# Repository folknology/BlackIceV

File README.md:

# BlackIce V
BlackIce V is the 6th generation of a long line of OpenSource Hardware FPGA boards designed by the myStorm community since 2016. Unlike it's predecessors based on the Ice40 HX range, the 'V' is based on the Lattice Ice40 UltraPlus up5K and offers great new features like DSP blocks and generous internal SRAM.

Current status is hardware design, you can see the developments we are making on my regular streams :
*  [Live Stream, 8pm BST](https://www.twitch.tv/folknology)
* [Historic streams](https://www.youtube.com/watch?v=79OoLG_Dxk0&list=PLXS9jyX9czzodpJNL-szsMfl0rOrZk4B7)
Or at the join us at the [myStorm community forum](https://forum.mystorm.uk)

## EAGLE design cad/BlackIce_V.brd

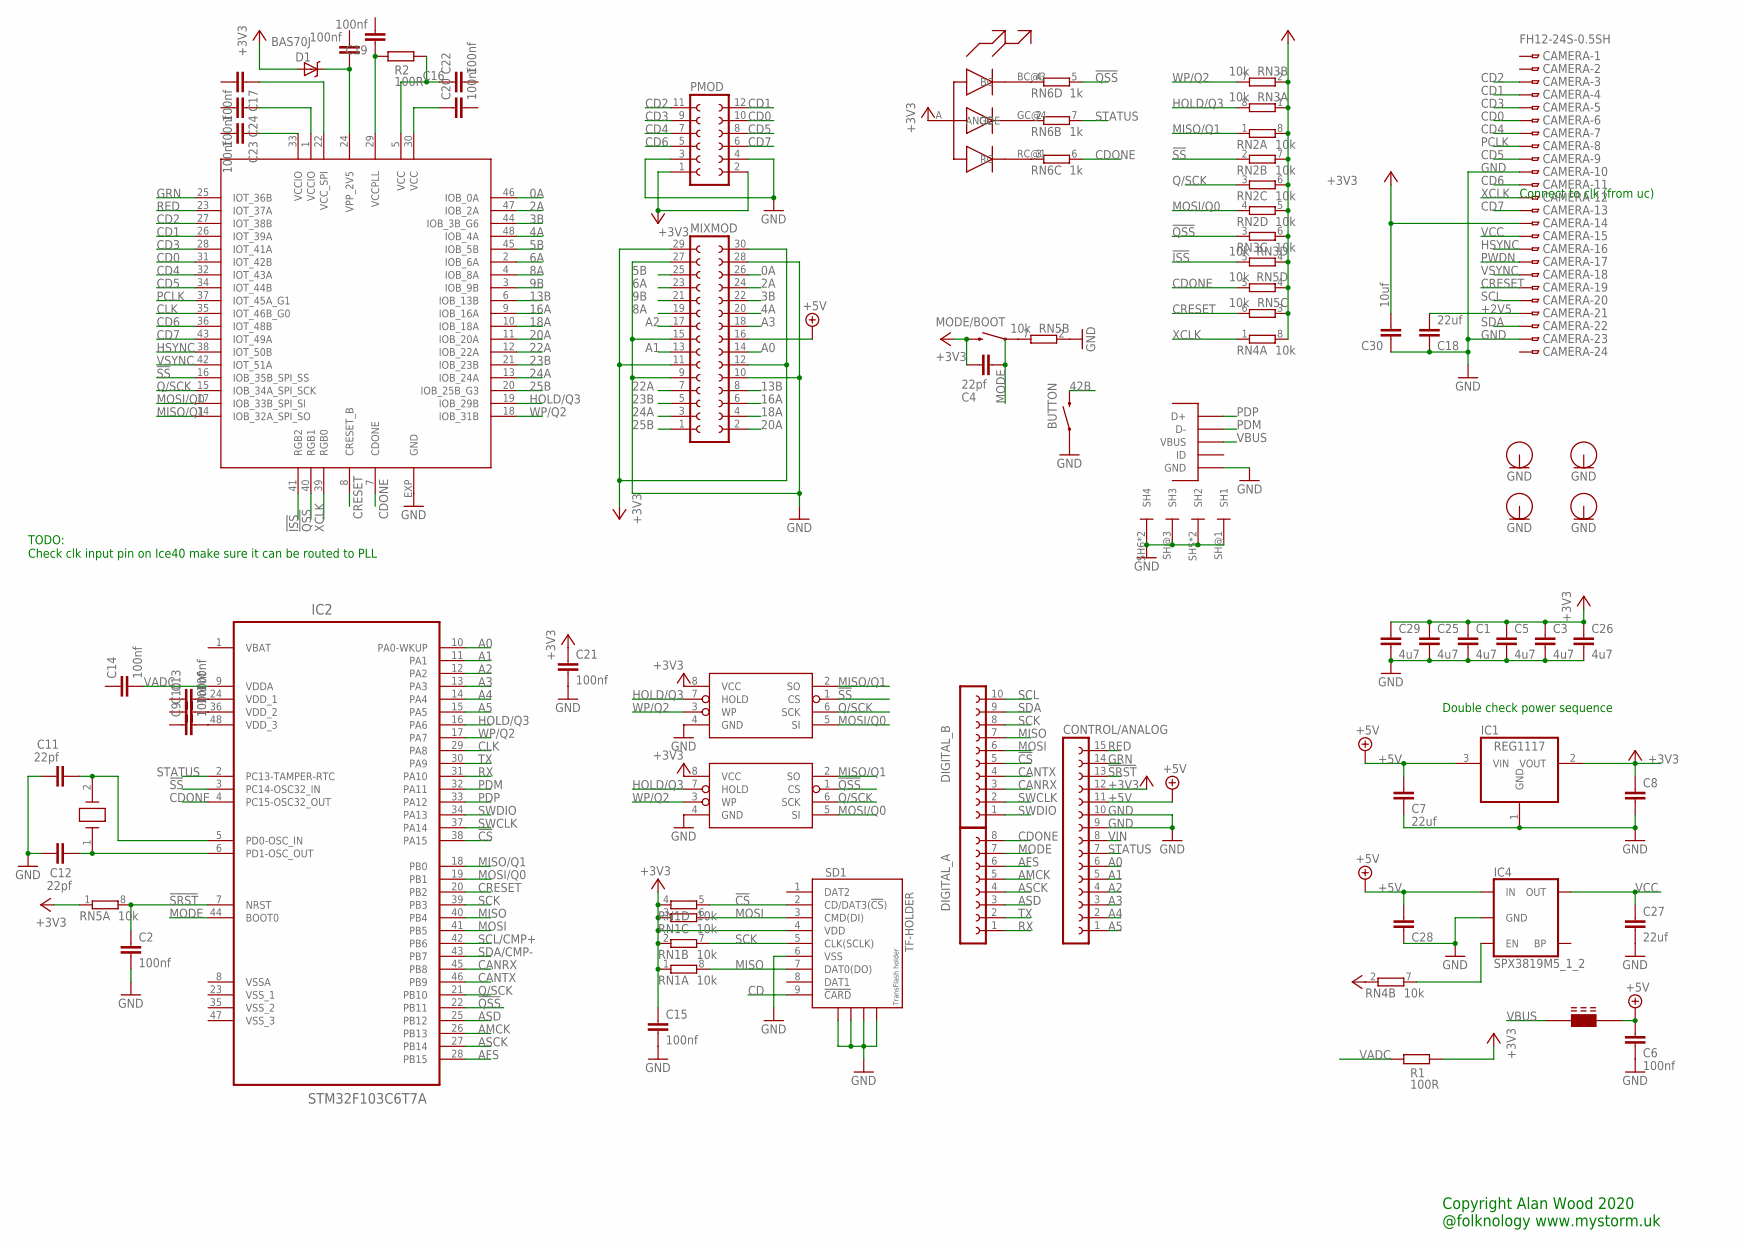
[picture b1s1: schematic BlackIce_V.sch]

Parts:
BUTTON: SWITCH-MOMENTARY-2SMD-1101NE; TACTILE-SWITCH-1101NE
C1, C3, C5, C25, C26, C29: 4u7; C0603
C2, C6, C9, C10, C13, C14, C15, C16, C17, C19, C20, C21, C22, C23, C24: 100nf; C0402
C4, C11, C12: 22pf; C0603
C7, C8, C18, C27, C28: 22uf; C0603
C30: 10uf; C0603
CAMERA: FH12-24S-0.5SH
CONTROL/ANALOG: FE15-1; FE15
D1: BAS70J; SOD-323
DIGITAL_A: FE08-1; FE08
DIGITAL_B: FE10-1; FE10
FB1: FERRITE_BEAD; 0603
H1, H2, H3, H4: HOLE2.5MM; 2.5MM-HOLE
IC1: REG1117; SOT223
IC2: STM32F103C6T7A; QFP50P900X900X160-48N
IC3: ICE40UP5K; QFN48
IC4: SPX3819M5_1_2; SOT23-5
IC5, IC6: AT25SDF041A; SOIC-8-NARROW
MIXMOD: FE15-2
MODE/BOOT: SWITCH-MOMENTARY-2SMD-1101NE; TACTILE-SWITCH-1101NE
PMOD: FE06-2W
R1, R2: 100R; R0402
RN1, RN2, RN3, RN4, RN5: 10k; 0603-ARV
RN6: 1k; 0603-ARV
SD1: TF-HOLDER; TF-PULL
U$1: FCI-MICROUSB-B-PEG; MICROUSB-B-PEG
U$4: RGB-PLCC-4; PLCC-4-SMALL
X1: HC49UP

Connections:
0A: IC3.46 (IOB_0A), MIXMOD.26
2A: IC3.47 (IOB_2A), MIXMOD.24
3B: IC3.44 (IOB_3B_G6), MIXMOD.22
4A: IC3.48 (IOB_4A), MIXMOD.20
5B: IC3.45 (IOB_5B), MIXMOD.25
6A: IC3.2 (IOB_6A), MIXMOD.23
8A: IC3.4 (IOB_8A), MIXMOD.19
9B: IC3.3 (IOB_9B), MIXMOD.21
13B: IC3.6 (IOB_13B), MIXMOD.8
16A: IC3.9 (IOB_16A), MIXMOD.6
18A: IC3.10 (IOB_18A), MIXMOD.4
20A: IC3.11 (IOB_20A), MIXMOD.2
22A: IC3.12 (IOB_22A), MIXMOD.7
23B: IC3.21 (IOB_23B), MIXMOD.5
24A: IC3.13 (IOB_24A), MIXMOD.3
25B: IC3.20 (IOB_25B_G3), MIXMOD.1
42B: BUTTON.2
!CS: DIGITAL_B.5, IC2.38 (PA15), RN1.5 (2), SD1.2 (CD/DAT3(!CS!))
!ISS: IC3.41 (RGB2), RN3.5 (2)
!QSS: IC2.22 (PB11), IC3.40 (RGB1), IC6.1 (CS), RN3.3 (1), RN6.5 (2)
!SRST: C2.1, CONTROL/ANALOG.13, IC2.7 (NRST), RN5.8 (2)
!SS: IC2.3 (PC14-OSC32_IN), IC3.16 (IOB_35B_SPI_SS), IC5.1 (CS), RN2.2 (1)
+2V5: C16.1, C18.1, CAMERA.21, D1.C, IC3.24 (VPP_2V5)
+3V3: C1.1, C3.1, C4.2, C5.1, C8.1, C15.1, C21.1, C25.1, C26.1, C29.1, C30.2, CAMERA.14, CONTROL/ANALOG.12, D1.A, IC1.2 (VOUT), IC5.8 (VCC), IC6.8 (VCC), MIXMOD.11, MIXMOD.12, MIXMOD.29, MIXMOD.30, MODE/BOOT.2, PMOD.1, PMOD.2, R1.1, RN1.1, RN1.2 (1), RN1.3 (1), RN1.4 (1), RN2.5 (2), RN2.6 (2), RN2.7 (2), RN2.8 (2), RN3.1, RN3.2 (1), RN3.4 (1), RN3.6 (2), RN4.2 (1), RN4.8 (2), RN5.1, RN5.3 (1), RN5.4 (1), SD1.4 (VDD), U$4.A (ANODE)
+5V: C6.2, C7.2, C28.2, CONTROL/ANALOG.11, FB1.2, IC1.3 (VIN), IC4.1 (IN), MIXMOD.16
A0: CONTROL/ANALOG.6, IC2.10 (PA0-WKUP), MIXMOD.14
A1: CONTROL/ANALOG.5, IC2.11 (PA1), MIXMOD.13
A2: CONTROL/ANALOG.4, IC2.12 (PA2), MIXMOD.17
A3: CONTROL/ANALOG.3, IC2.13 (PA3), MIXMOD.18
A4: CONTROL/ANALOG.2, IC2.14 (PA4)
A5: CONTROL/ANALOG.1, IC2.15 (PA5)
AFS: DIGITAL_A.6, IC2.28 (PB15)
AMCK: DIGITAL_A.5, IC2.26 (PB13)
ASCK: DIGITAL_A.4, IC2.27 (PB14)
ASD: DIGITAL_A.3, IC2.25 (PB12)
CANRX: DIGITAL_B.3, IC2.45 (PB8)
CANTX: DIGITAL_B.4, IC2.46 (PB9)
CD: SD1.9 (!CARD)
CD0: CAMERA.6, IC3.31 (IOT_42B), PMOD.10
CD1: CAMERA.4, IC3.26 (IOT_39A), PMOD.12
CD2: CAMERA.3, IC3.27 (IOT_38B), PMOD.11
CD3: CAMERA.5, IC3.28 (IOT_41A), PMOD.9
CD4: CAMERA.7, IC3.32 (IOT_43A), PMOD.7
CD5: CAMERA.9, IC3.34 (IOT_44B), PMOD.8
CD6: CAMERA.11, IC3.36 (IOT_48B), PMOD.5
CD7: CAMERA.13, IC3.43 (IOT_49A), PMOD.6
CDONE: DIGITAL_A.8, IC2.4 (PC15-OSC32_OUT), IC3.7 (CDONE), RN5.5 (2), RN6.6 (2)
CLK: IC2.29 (PA8), IC3.35 (IOT_46B_G0)
CRESET: CAMERA.19, IC2.20 (PB2), IC3.8 (CRESET_B), RN5.6 (2)
GND: BUTTON.1, C1.2, C2.2, C3.2, C5.2, C6.1, C7.1, C8.2, C11.1, C12.1, C15.2, C18.2, C21.2, C25.2, C26.2, C27.2, C28.1, C29.2, C30.1, CAMERA.10, CAMERA.23, CONTROL/ANALOG.9, CONTROL/ANALOG.10, H1.P$1, H2.P$1, H3.P$1, H4.P$1, IC1.1 (GND), IC3.EXP (GND), IC4.2 (GND), IC5.4 (GND), IC6.4 (GND), MIXMOD.9, MIXMOD.10, MIXMOD.15, MIXMOD.27, MIXMOD.28, PMOD.3, PMOD.4, RN5.2 (1), SD1.6 (VSS), SD1.S1, SD1.S2, SD1.S3, SD1.S4, U$1.P$5 (GND), U$1.SH5 (SH2), U$1.SH6 (SH4), U$1.SH@1 (SH1), U$1.SH@2 (SH2), U$1.SH@3 (SH3), U$1.SH@4 (SH4)
GRN: CONTROL/ANALOG.14, IC3.25 (IOT_36B)
HOLD/Q3: IC2.16 (PA6), IC3.19 (IOB_29B), IC5.7 (HOLD), IC6.7 (HOLD), RN3.8 (2)
HSYNC: CAMERA.16, IC3.38 (IOT_50B)
MISO: DIGITAL_B.7, IC2.40 (PB4), RN1.8 (2), SD1.7 (DAT0(DO))
MISO/Q1: IC2.18 (PB0), IC3.14 (IOB_32A_SPI_SO), IC5.2 (SO), IC6.2 (SO), RN2.1
MODE: C4.1, DIGITAL_A.7, IC2.44 (BOOT0)
MOSI: DIGITAL_B.6, IC2.41 (PB5), RN1.6 (2), SD1.3 (CMD(DI))
MOSI/Q0: IC2.19 (PB1), IC3.17 (IOB_33B_SPI_SI), IC5.5 (SI), IC6.5 (SI), RN2.4 (1)
unnamed: RN6.4 (1), U$4.BC@3 (BC)
unnamed: RN6.2 (1), U$4.GC@4 (GC)
unnamed: RN6.3 (1), U$4.RC@1 (RC)
unnamed: MODE/BOOT.1, RN5.7 (2)
unnamed: IC4.3 (EN), RN4.7 (2)
unnamed: C12.2, IC2.6 (PD1-OSC_OUT), X1.1 (X1)
unnamed: C11.2, IC2.5 (PD0-OSC_IN), X1.2 (X2)
unnamed: C13.2, IC2.24 (VDD_1)
unnamed: C10.2, IC2.36 (VDD_2)
unnamed: C9.2, IC2.48 (VDD_3)
unnamed: C23.1, IC3.33 (VCCIO)
unnamed: C24.1, IC3.1 (VCCIO)
unnamed: C17.1, IC3.22 (VCC_SPI)
unnamed: C19.1, IC3.29 (VCCPLL), R2.2
unnamed: C22.1, IC3.5 (VCC), R2.1
unnamed: C20.1, IC3.30 (VCC)
PCLK: CAMERA.8, IC3.37 (IOT_45A_G1)
PDM: IC2.32 (PA11), U$1.P$2 (D-)
PDP: IC2.33 (PA12), U$1.P$3 (D+)
PWDN: CAMERA.17
Q/SCK: IC2.21 (PB10), IC3.15 (IOB_34A_SPI_SCK), IC5.6 (SCK), IC6.6 (SCK), RN2.3 (1)
RED: CONTROL/ANALOG.15, IC3.23 (IOT_37A)
RX: DIGITAL_A.1, IC2.31 (PA10)
SCK: DIGITAL_B.8, IC2.39 (PB3), RN1.7 (2), SD1.5 (CLK(SCLK))
SCL: CAMERA.20, DIGITAL_B.10
SCL/CMP+: IC2.42 (PB6)
SDA: CAMERA.22, DIGITAL_B.9
SDA/CMP-: IC2.43 (PB7)
STATUS: CONTROL/ANALOG.7, IC2.2 (PC13-TAMPER-RTC)
SWCLK: DIGITAL_B.2, IC2.37 (PA14)
SWDIO: DIGITAL_B.1, IC2.34 (PA13)
TX: DIGITAL_A.2, IC2.30 (PA9)
VADC: C14.2, IC2.9 (VDDA), R1.2
VBAT: IC2.1 (VBAT)
VBUS: FB1.1, U$1.P$1 (VBUS)
VCC: C27.1, CAMERA.15, IC4.5 (OUT)
VIN: CONTROL/ANALOG.8
VSYNC: CAMERA.18, IC3.42 (IOT_51A)
WP/Q2: IC2.17 (PA7), IC3.18 (IOB_31B), IC5.3 (WP), IC6.3 (WP), RN3.7 (2)
XCLK: CAMERA.12, IC3.39 (RGB0), RN4.1

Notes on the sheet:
Double check power sequence
TODO: Check clk input pin on Ice40 make sure it can be routed to PLL
Connect to clk (from uc)
Copyright Alan Wood 2020 @folknology www.mystorm.uk

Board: 4 copper layers, 62 parts (0 on the bottom side), 91 nets, no tracks yet.

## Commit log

2020-09-19 Added the design and support files from local repo, community agreed name
2020-09-19 Corrected some typos
2020-09-19 Cleaned up the schematic a little and soretyed the Pmod signals (shared with Cam data)
2020-09-19 Update the Schmatic image to a recent version

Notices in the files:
cad/BlackIce_V.brd:
Copyright 2020 Alan Wood
parts and their libraries:
SparkFun-Electromechanical: Licensing: Creative Commons ShareAlike 4.0 International - https://creativecommons.org/licenses/by-sa/4.0
